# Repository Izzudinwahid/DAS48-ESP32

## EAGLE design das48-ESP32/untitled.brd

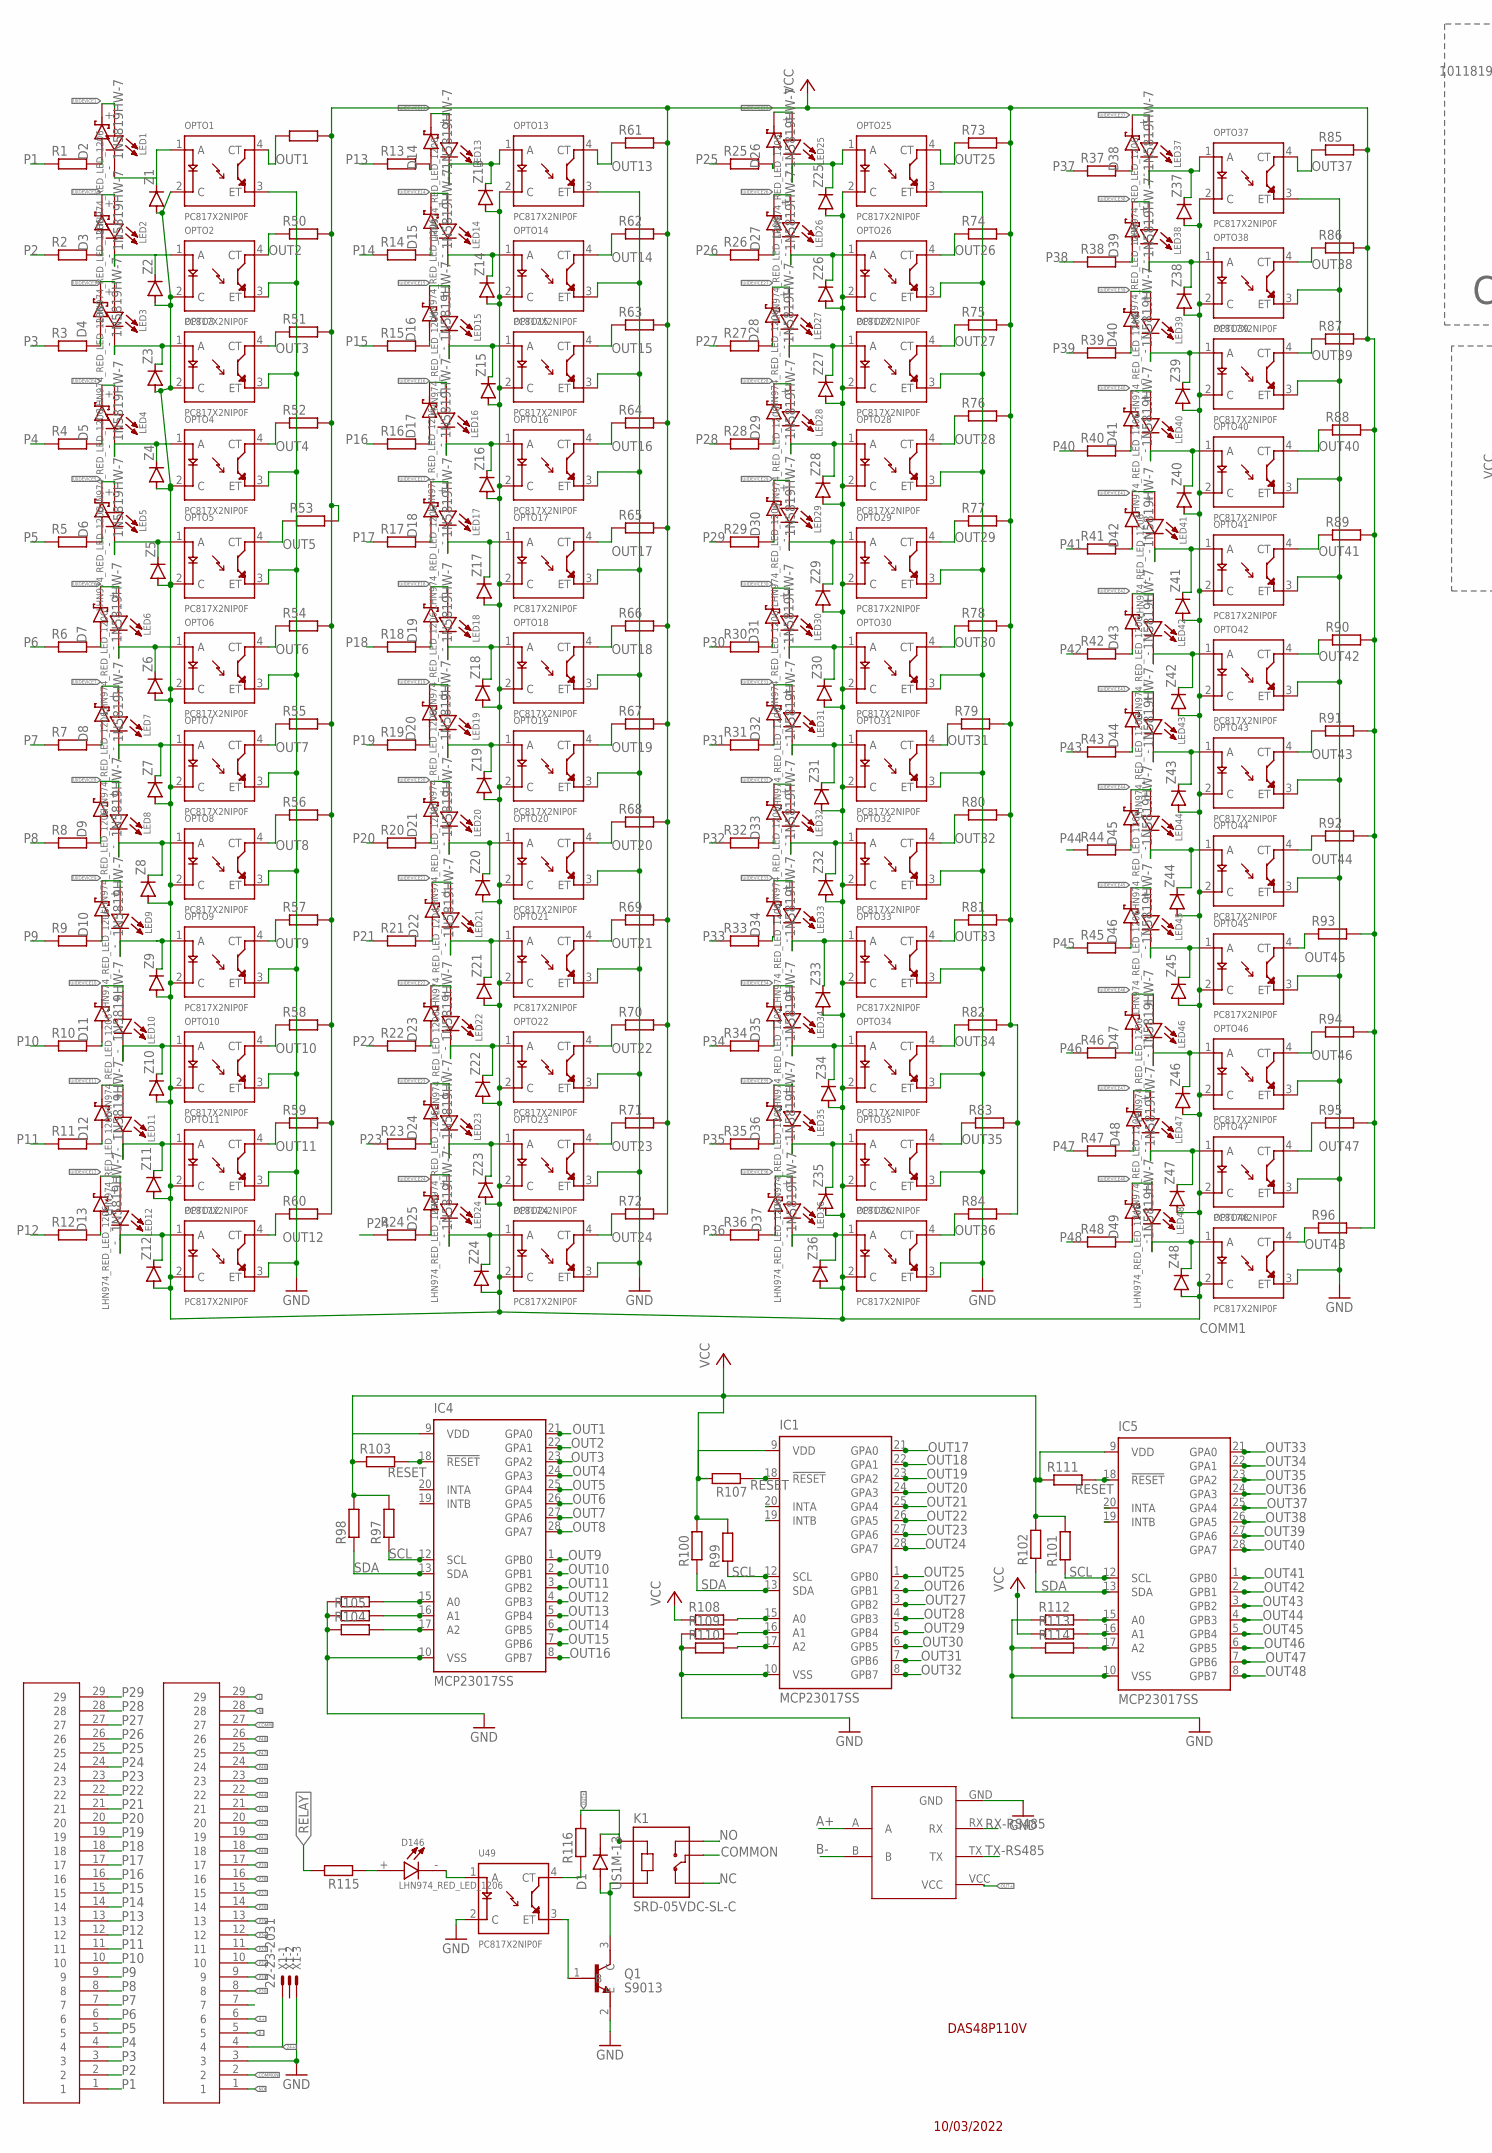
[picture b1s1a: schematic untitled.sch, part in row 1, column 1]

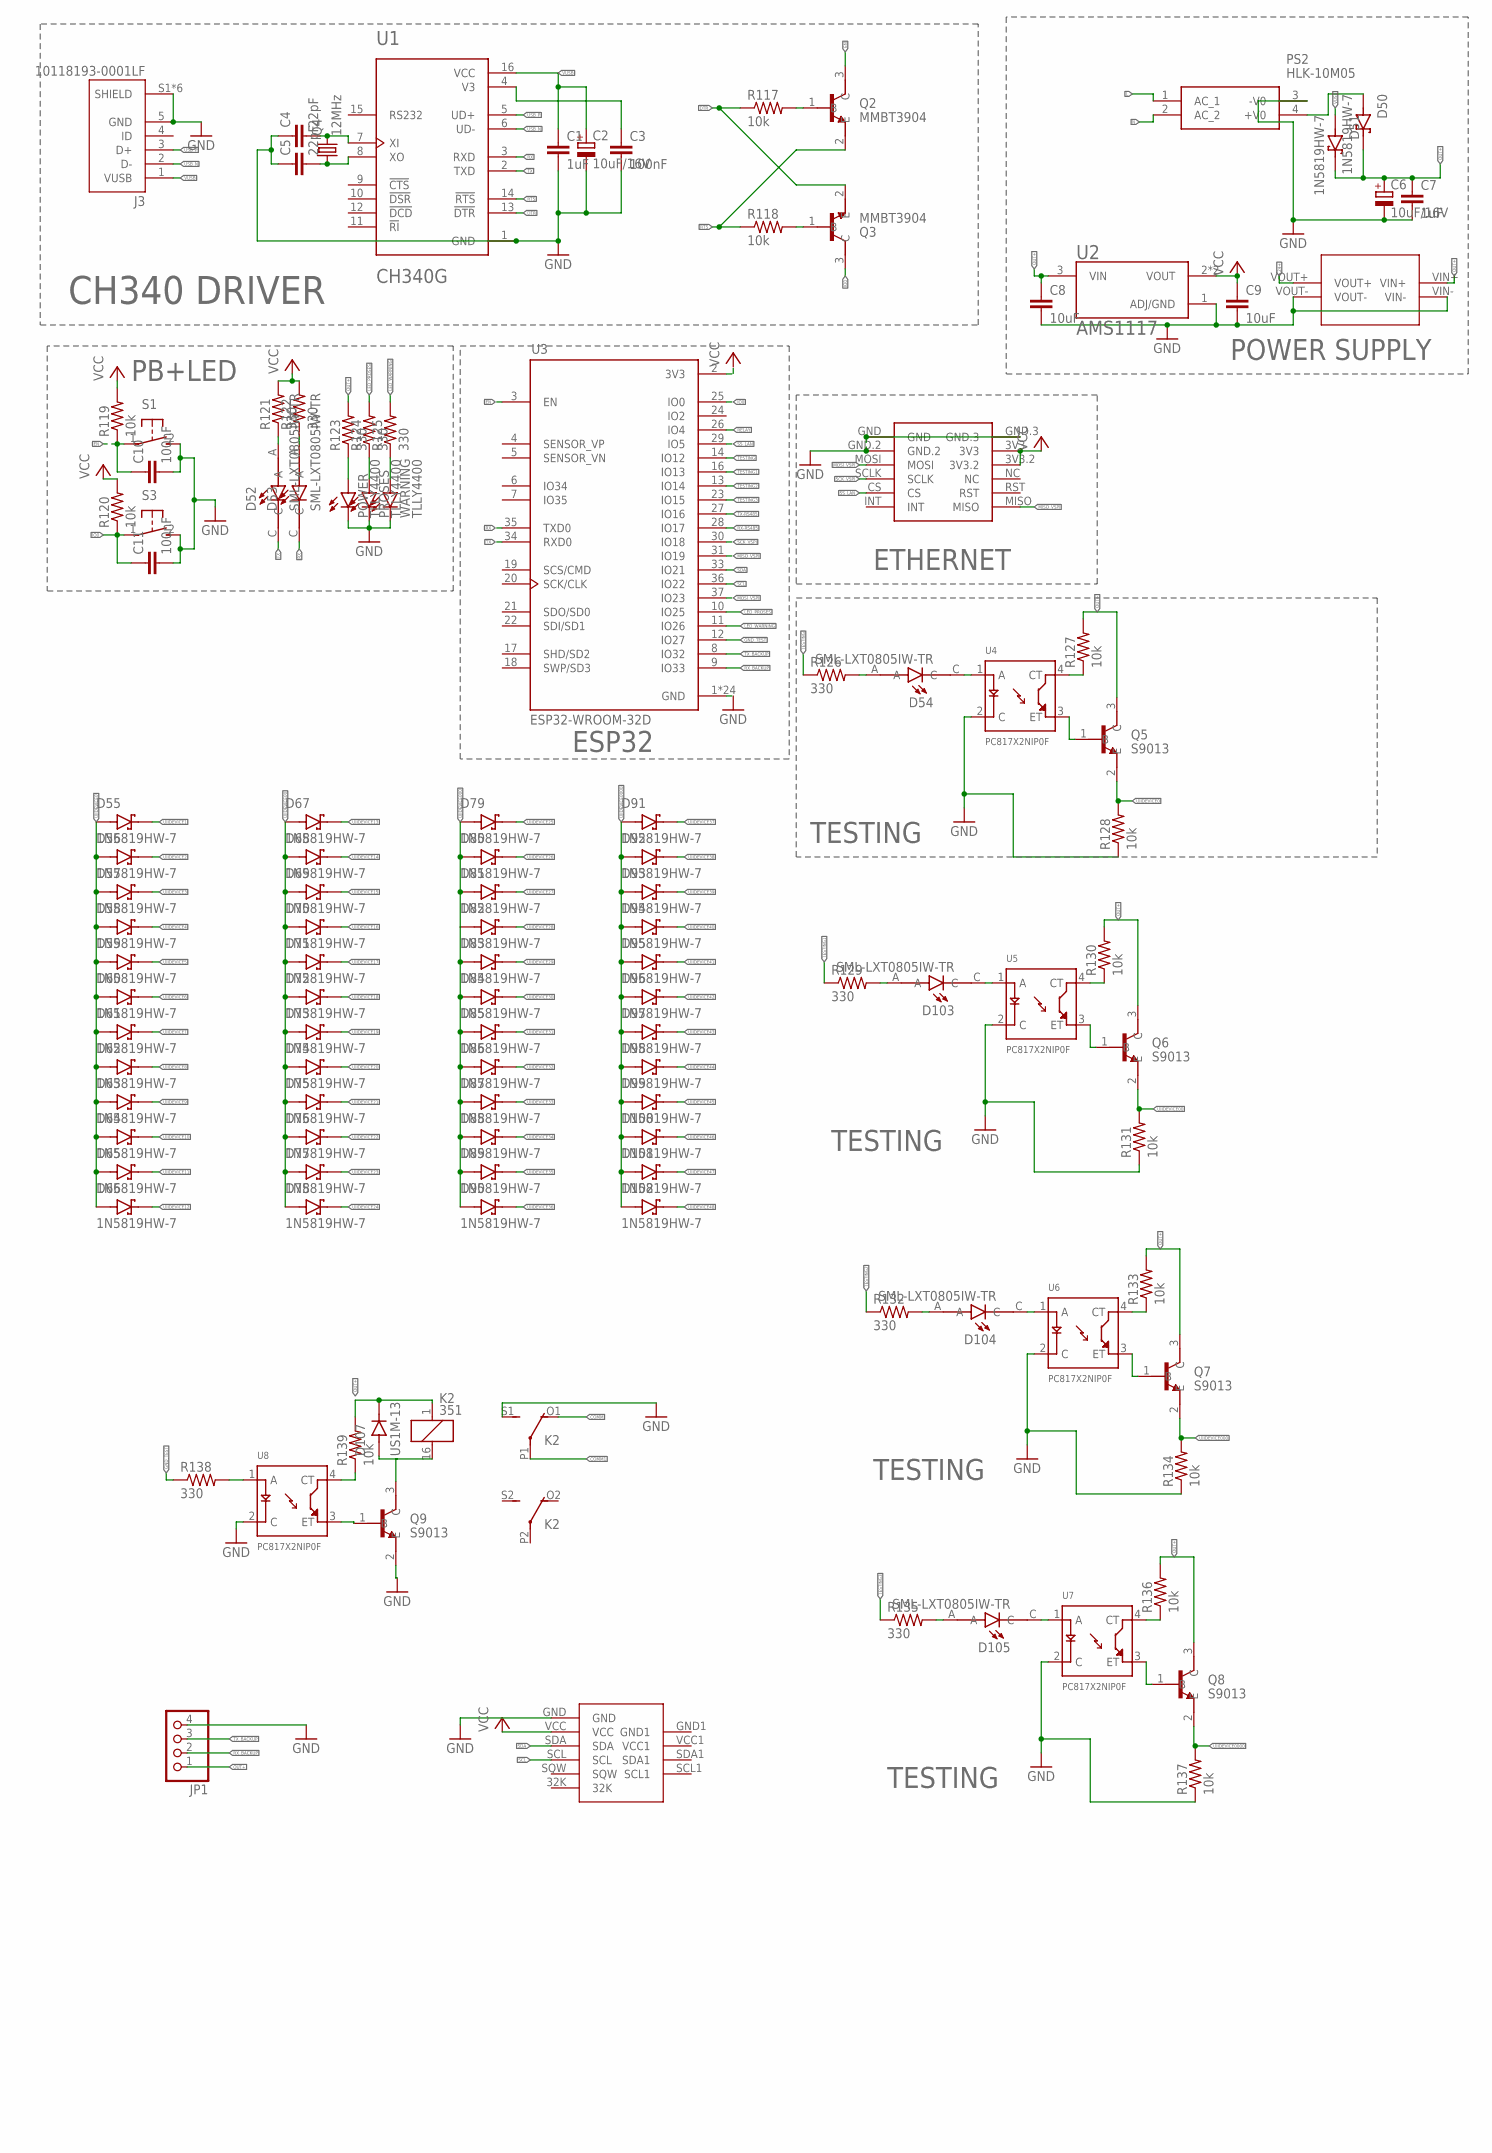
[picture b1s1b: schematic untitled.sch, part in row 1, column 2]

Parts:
C1, C7: 1uF; C0805K
C2, C6: 10uF/16V; 153CLV-0505
C3, C10, C11: 100nF; C0805K
C4, C5: 22pF; C0805K
C8, C9: 10uF; C0805K
D1, D107: US1M-13; DIOM5226X240N
D2, D3, D4, D5, D6, D7, D8, D9, D10, D11, D12, D13, D14, D15, D16, D17, D18, D19, D20, D21, D22, D23, D24, D25, D26, D27, D28, D29, D30, D31, D32, D33, D34, D35, D36, D37, D38, D39, D40, D41, D42, D43, D44, D45, D46, D47, D48, D49, D50, D51, D55, D56, D57, D58, D59, D60, D61, D62, D63, D64, D65, D66, D67, D68, D69, D70, D71, D72, D73, D74, D75, D76, D77, D78, D79, D80, D81, D82, D83, D84, D85, D86, D87, D88, D89, D90, D91, D92, D93, D94, D95, D96, D97, D98, D99, D100, D101, D102: 1N5819HW-7; SOD3715X145N
D52, D53, D54, D103, D104, D105: SML-LXT0805IW-TR; LEDC2012X120N
D146: LHN974_RED_LED_1206; LEDC3216X120N
HEADER-29P1, HEADER-29P2: HEADER-29P
IC1, IC4, IC5: MCP23017SS; SSOP28DB
J3: 10118193-0001LF; FCI_10118193-0001LF
JP1: PINHD-1X4; 1X04
K1: SRD-05VDC-SL-C; RELAY_SRD-05VDC-SL-C
K2: 351
LED1, LED2, LED3, LED4, LED5, LED6, LED7, LED8, LED9, LED10, LED11, LED12, LED13, LED14, LED15, LED16, LED17, LED18, LED19, LED20, LED21, LED22, LED23, LED24, LED25, LED26, LED27, LED28, LED29, LED30, LED31, LED32, LED33, LED34, LED35, LED36, LED37, LED38, LED39, LED40, LED41, LED42, LED43, LED44, LED45, LED46, LED47, LED48: LHN974_RED_LED_1206; LEDC3216X120N
MT1: MT3608
OPTO1, OPTO2, OPTO3, OPTO4, OPTO5, OPTO6, OPTO7, OPTO8, OPTO9, OPTO10, OPTO11, OPTO12, OPTO13, OPTO14, OPTO15, OPTO16, OPTO17, OPTO18, OPTO19, OPTO20, OPTO21, OPTO22, OPTO23, OPTO24, OPTO25, OPTO26, OPTO27, OPTO28, OPTO29, OPTO30, OPTO31, OPTO32, OPTO33, OPTO34, OPTO35, OPTO36, OPTO37, OPTO38, OPTO39, OPTO40, OPTO41, OPTO42, OPTO43, OPTO44, OPTO45, OPTO46, OPTO47, OPTO48: PC817X2NIP0F; SOT254P975X400-4N
POWER: TLLY4400; LED3MM
PROSES: TLLY4400; LED3MM
PS2: HLK-10M05; HLK10M05
Q1, Q5, Q6, Q7, Q8, Q9: S9013; SOT95P240X120-3N
Q2, Q3: MMBT3904; SOT95P240X120-3N
Q4: 12MHz; SM49
R1, R2, R3, R4, R5, R6, R7, R8, R9, R10, R11, R12, R13, R14, R15, R16, R17, R18, R19, R20, R21, R22, R23, R24, R25, R26, R27, R28, R29, R30, R31, R32, R33, R34, R35, R36, R37, R38, R39, R40, R41, R42, R43, R44, R45, R46, R47, R48: R-EU_0617/17; 0617/17
R49, R50, R51, R52, R53, R54, R55, R56, R57, R58, R59, R60, R61, R62, R63, R64, R65, R66, R67, R68, R69, R70, R71, R72, R73, R74, R75, R76, R77, R78, R79, R80, R81, R82, R83, R84, R85, R86, R87, R88, R89, R90, R91, R92, R93, R94, R95, R96, R97, R98, R99, R100, R101, R102, R103, R104, R105, R106, R107, R108, R109, R110, R111, R112, R113, R114, R115, R116: R-EU_R0805; R0805
R117, R118, R119, R120, R127, R128, R130, R131, R133, R134, R136, R137, R139: 10k; M0805
R121, R122, R123, R124, R125, R126, R129, R132, R135, R138: 330; M0805
RTC1: RTC3231
S1, S3: 31-XX; B3F-31XX
TTL-RS1: TTL-RS485
U1: CH340G; SOIC127P600X180-16N
U2: AMS1117; SOT229P700X180-4N
U3: ESP32-WROOM-32D; MODULE_ESP32-WROOM-32D
U4, U5, U6, U7, U8, U49: PC817X2NIP0F; SOT254P975X400-4N
U$1: MINI_W5500
WARNING: TLLY4400; LED3MM
X1: 22-23-2031
Z1, Z2, Z3, Z4, Z5, Z6, Z7, Z8, Z9, Z10, Z11, Z12, Z13, Z14, Z15, Z16, Z17, Z18, Z19, Z20, Z21, Z22, Z23, Z24, Z25, Z26, Z27, Z28, Z29, Z30, Z31, Z32, Z33, Z34, Z35, Z36, Z37, Z38, Z39, Z40, Z41, Z42, Z43, Z44, Z45, Z46, Z47, Z48: DIODE-SOD123; SOD123

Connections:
24+: HEADER-29P2.4, MT1.VOUT+, X1.1
A+: HEADER-29P2.6, TTL-RS1.A
B-: HEADER-29P2.5, TTL-RS1.B
COMM: HEADER-29P2.27, K2.O1 (O)
COMM1: K2.P1, OPTO1.2 (C), OPTO2.2 (C), OPTO3.2 (C), OPTO4.2 (C), OPTO5.2 (C), OPTO6.2 (C), OPTO7.2 (C), OPTO8.2 (C), OPTO9.2 (C), OPTO10.2 (C), OPTO11.2 (C), OPTO12.2 (C), OPTO13.2 (C), OPTO14.2 (C), OPTO15.2 (C), OPTO16.2 (C), OPTO17.2 (C), OPTO18.2 (C), OPTO19.2 (C), OPTO20.2 (C), OPTO21.2 (C), OPTO22.2 (C), OPTO23.2 (C), OPTO24.2 (C), OPTO25.2 (C), OPTO26.2 (C), OPTO27.2 (C), OPTO28.2 (C), OPTO29.2 (C), OPTO30.2 (C), OPTO31.2 (C), OPTO32.2 (C), OPTO33.2 (C), OPTO34.2 (C), OPTO35.2 (C), OPTO36.2 (C), OPTO37.2 (C), OPTO38.2 (C), OPTO39.2 (C), OPTO40.2 (C), OPTO41.2 (C), OPTO42.2 (C), OPTO43.2 (C), OPTO44.2 (C), OPTO45.2 (C), OPTO46.2 (C), OPTO47.2 (C), OPTO48.2 (C), Z1.A, Z2.A, Z3.A, Z4.A, Z5.A, Z6.A, Z7.A, Z8.A, Z9.A, Z10.A, Z11.A, Z12.A, Z13.A, Z14.A, Z15.A, Z16.A, Z17.A, Z18.A, Z19.A, Z20.A, Z21.A, Z22.A, Z23.A, Z24.A, Z25.A, Z26.A, Z27.A, Z28.A, Z29.A, Z30.A, Z31.A, Z32.A, Z33.A, Z34.A, Z35.A, Z36.A, Z37.A, Z38.A, Z39.A, Z40.A, Z41.A, Z42.A, Z43.A, Z44.A, Z45.A, Z46.A, Z47.A, Z48.A
COMMON: HEADER-29P2.2, K1.COM
DTR: Q3.2 (E), R117.1, U1.13 (!DTR)
EN: C10.1, Q2.3 (C), R119.1, S1.1, U3.3 (EN)
GND: C1.2, C2.-, C3.2, C4.1, C5.1, C6.-, C7.2, C8.2, C9.2, C10.2, C11.2, HEADER-29P2.3, IC1.10 (VSS), IC4.10 (VSS), IC5.10 (VSS), J3.5 (GND), J3.S1 (SHIELD), J3.S2 (SHIELD), J3.S3 (SHIELD), J3.S4 (SHIELD), J3.S5 (SHIELD), J3.S6 (SHIELD), JP1.4, K2.S1 (S), MT1.VIN-, MT1.VOUT-, OPTO1.3 (ET), OPTO2.3 (ET), OPTO3.3 (ET), OPTO4.3 (ET), OPTO5.3 (ET), OPTO6.3 (ET), OPTO7.3 (ET), OPTO8.3 (ET), OPTO9.3 (ET), OPTO10.3 (ET), OPTO11.3 (ET), OPTO12.3 (ET), OPTO13.3 (ET), OPTO14.3 (ET), OPTO15.3 (ET), OPTO16.3 (ET), OPTO17.3 (ET), OPTO18.3 (ET), OPTO19.3 (ET), OPTO20.3 (ET), OPTO21.3 (ET), OPTO22.3 (ET), OPTO23.3 (ET), OPTO24.3 (ET), OPTO25.3 (ET), OPTO26.3 (ET), OPTO27.3 (ET), OPTO28.3 (ET), OPTO29.3 (ET), OPTO30.3 (ET), OPTO31.3 (ET), OPTO32.3 (ET), OPTO33.3 (ET), OPTO34.3 (ET), OPTO35.3 (ET), OPTO36.3 (ET), OPTO37.3 (ET), OPTO38.3 (ET), OPTO39.3 (ET), OPTO40.3 (ET), OPTO41.3 (ET), OPTO42.3 (ET), OPTO43.3 (ET), OPTO44.3 (ET), OPTO45.3 (ET), OPTO46.3 (ET), OPTO47.3 (ET), OPTO48.3 (ET), POWER.K (C), PROSES.K (C), PS2.3 (-V0), Q1.2 (E), Q9.2 (E), R104.1, R105.1, R106.1, R109.1, R110.1, R112.1, R114.1, R128.1, R131.1, R134.1, R137.1, RTC1.GND, S1.2 (S), S3.2 (S), TTL-RS1.GND, U1.1 (GND), U2.1 (ADJ/GND), U3.1 (GND), U3.15 (GND), U3.38 (GND), U3.39_1 (GND), U3.39_2 (GND), U3.39_3 (GND), U3.39_4 (GND), U3.39_5 (GND), U3.39_6 (GND), U3.39_7 (GND), U3.39_8 (GND), U3.39_9 (GND), U3.39_10 (GND), U3.39_11 (GND), U3.39_12 (GND), U3.39_13 (GND), U3.39_14 (GND), U3.39_15 (GND), U3.39_16 (GND), U3.39_17 (GND), U3.39_18 (GND), U3.39_19 (GND), U3.39_20 (GND), U3.39_21 (GND), U4.2 (C), U5.2 (C), U6.2 (C), U7.2 (C), U8.2 (C), U49.2 (C), U$1.GND, U$1.GND.2, U$1.GND.3, WARNING.K (C), X1.3
GND_TEST: R138.1, U3.12 (IO27)
IO0: C11.1, Q3.3 (C), R120.1, S3.1, U3.25 (IO0)
L: HEADER-29P2.29, PS2.1 (AC_1)
LED_PROSES: R124.2, U3.10 (IO25)
LED_WARNING: R125.2, U3.11 (IO26)
MISO_VSPI: U3.31 (IO19), U$1.MISO
MOSI_VSPI: U3.37 (IO23), U$1.MOSI
N: HEADER-29P2.28, PS2.2 (AC_2)
unnamed: D2.A, R1.2
unnamed: D50.A, PS2.4 (+V0)
unnamed: D3.A, R2.2
unnamed: Q5.1 (B), U4.3 (ET)
unnamed: D4.A, R3.2
unnamed: R127.1, U4.4 (CT)
unnamed: D5.A, R4.2
unnamed: D103.A, R129.2
unnamed: D6.A, R5.2
unnamed: D103.C, U5.1 (A)
unnamed: D7.A, R6.2
unnamed: Q6.1 (B), U5.3 (ET)
unnamed: D8.A, R7.2
unnamed: R130.1, U5.4 (CT)
unnamed: D9.A, R8.2
unnamed: D104.A, R132.2
unnamed: D15.A, R14.2
unnamed: LED1.-, OPTO1.1 (A), Z1.C
unnamed: LED13.-, OPTO13.1 (A), Z13.C
unnamed: D10.A, R9.2
unnamed: LED14.-, OPTO14.1 (A), Z14.C
unnamed: D104.C, U6.1 (A)
unnamed: LED15.-, OPTO15.1 (A), Z15.C
unnamed: D11.A, R10.2
unnamed: LED16.-, OPTO16.1 (A), Z16.C
unnamed: Q7.1 (B), U6.3 (ET)
unnamed: LED17.-, OPTO17.1 (A), Z17.C
unnamed: D12.A, R11.2
unnamed: LED18.-, OPTO18.1 (A), Z18.C
unnamed: R133.1, U6.4 (CT)
unnamed: LED19.-, OPTO19.1 (A), Z19.C
unnamed: LED20.-, OPTO20.1 (A), Z20.C
unnamed: LED21.-, OPTO21.1 (A), Z21.C
unnamed: D105.A, R135.2
unnamed: LED22.-, OPTO22.1 (A), Z22.C
unnamed: D13.A, R12.2
unnamed: LED23.-, OPTO23.1 (A), Z23.C
unnamed: D105.C, U7.1 (A)
unnamed: LED24.-, OPTO24.1 (A), Z24.C
unnamed: D14.A, R13.2
unnamed: LED25.-, OPTO25.1 (A), Z25.C
unnamed: Q8.1 (B), U7.3 (ET)
unnamed: LED26.-, OPTO26.1 (A), Z26.C
unnamed: D16.A, R15.2
unnamed: LED27.-, OPTO27.1 (A), Z27.C
unnamed: R136.1, U7.4 (CT)
unnamed: LED28.-, OPTO28.1 (A), Z28.C
unnamed: D17.A, R16.2
unnamed: LED29.-, OPTO29.1 (A), Z29.C
unnamed: LED30.-, OPTO30.1 (A), Z30.C
unnamed: D18.A, R17.2
unnamed: LED31.-, OPTO31.1 (A), Z31.C
unnamed: R138.2, U8.1 (A)
unnamed: LED32.-, OPTO32.1 (A), Z32.C
unnamed: D19.A, R18.2
unnamed: LED33.-, OPTO33.1 (A), Z33.C
unnamed: R139.1, U8.4 (CT)
unnamed: LED34.-, OPTO34.1 (A), Z34.C
unnamed: D20.A, R19.2
unnamed: LED35.-, OPTO35.1 (A), Z35.C
unnamed: Q9.1 (B), U8.3 (ET)
unnamed: LED36.-, OPTO36.1 (A), Z36.C
unnamed: D32.A, R31.2
unnamed: LED37.-, OPTO37.1 (A), Z37.C
unnamed: D21.A, R20.2
unnamed: LED38.-, OPTO38.1 (A), Z38.C
unnamed: LED39.-, OPTO39.1 (A), Z39.C
unnamed: LED40.-, OPTO40.1 (A), Z40.C
unnamed: D22.A, R21.2
unnamed: LED41.-, OPTO41.1 (A), Z41.C
unnamed: D107.A, K2.16 (2), Q9.3 (C)
unnamed: LED42.-, OPTO42.1 (A), Z42.C
unnamed: LED43.-, OPTO43.1 (A), Z43.C
unnamed: D23.A, R22.2
unnamed: LED44.-, OPTO44.1 (A), Z44.C
unnamed: LED45.-, OPTO45.1 (A), Z45.C
unnamed: D24.A, R23.2
unnamed: LED46.-, OPTO46.1 (A), Z46.C
unnamed: LED47.-, OPTO47.1 (A), Z47.C
unnamed: D25.A, R24.2
unnamed: LED48.-, OPTO48.1 (A), Z48.C
unnamed: LED2.-, OPTO2.1 (A), Z2.C
unnamed: LED3.-, OPTO3.1 (A), Z3.C
unnamed: LED4.-, OPTO4.1 (A), Z4.C
unnamed: LED5.-, OPTO5.1 (A), Z5.C
unnamed: LED6.-, OPTO6.1 (A), Z6.C
unnamed: LED7.-, OPTO7.1 (A), Z7.C
unnamed: LED8.-, OPTO8.1 (A), Z8.C
unnamed: LED9.-, OPTO9.1 (A), Z9.C
unnamed: LED10.-, OPTO10.1 (A), Z10.C
unnamed: LED11.-, OPTO11.1 (A), Z11.C
unnamed: LED12.-, OPTO12.1 (A), Z12.C
unnamed: D146.-, U49.1 (A)
unnamed: D146.+, R115.1
unnamed: R116.1, U49.4 (CT)
unnamed: IC5.15 (A0), R112.2
unnamed: D1.A, K1.A2, Q1.3 (C)
unnamed: Q1.1 (B), U49.3 (ET)
unnamed: IC5.16 (A1), R113.2
unnamed: D26.A, R25.2
unnamed: IC1.15 (A0), R108.2
unnamed: IC1.16 (A1), R109.2
unnamed: IC4.15 (A0), R106.2
unnamed: IC4.16 (A1), R105.2
unnamed: IC4.17 (A2), R104.2
unnamed: IC5.17 (A2), R114.2
unnamed: IC1.17 (A2), R110.2
unnamed: D27.A, R26.2
unnamed: D28.A, R27.2
unnamed: D29.A, R28.2
unnamed: D30.A, R29.2
unnamed: D31.A, R30.2
unnamed: D33.A, R32.2
unnamed: D35.A, R34.2
unnamed: D36.A, R35.2
unnamed: D42.A, R41.2
unnamed: D37.A, R36.2
unnamed: D38.A, R37.2
unnamed: D34.A, R33.2
unnamed: D39.A, R38.2
unnamed: D40.A, R39.2
unnamed: D41.A, R40.2
unnamed: D43.A, R42.2
unnamed: D44.A, R43.2
unnamed: D45.A, R44.2
unnamed: D46.A, R45.2
unnamed: D47.A, R46.2
unnamed: D54.A, R126.2
unnamed: D54.C, U4.1 (A)
unnamed: D48.A, R47.2
unnamed: D49.A, R48.2
unnamed: C3.1, U1.4 (V3)
unnamed: C4.2, Q4.2, U1.7 (XI)
unnamed: C5.2, Q4.1, U1.8 (XO)
unnamed: POWER.A, R123.1
unnamed: PROSES.A, R124.1
unnamed: Q2.1 (B), R117.2
unnamed: Q3.1 (B), R118.2
unnamed: R125.1, WARNING.A
unnamed: D52.A, R121.1
unnamed: D53.A, R122.1
NC: K1.NC
NO: HEADER-29P2.1, K1.NO
OUT1: IC4.21 (GPA0), OPTO1.4 (CT), R49.1
OUT2: IC4.22 (GPA1), OPTO2.4 (CT), R50.1
OUT3: IC4.23 (GPA2), OPTO3.4 (CT), R51.1
OUT4: IC4.24 (GPA3), OPTO4.4 (CT), R52.1
OUT5: IC4.25 (GPA4), OPTO5.4 (CT), R53.1
OUT6: IC4.26 (GPA5), OPTO6.4 (CT), R54.1
OUT7: IC4.27 (GPA6), OPTO7.4 (CT), R55.1
OUT8: IC4.28 (GPA7), OPTO8.4 (CT), R56.1
OUT9: IC4.1 (GPB0), OPTO9.4 (CT), R57.1
OUT10: IC4.2 (GPB1), OPTO10.4 (CT), R58.1
OUT11: IC4.3 (GPB2), OPTO11.4 (CT), R59.1
OUT12: IC4.4 (GPB3), OPTO12.4 (CT), R60.1
OUT13: IC4.5 (GPB4), OPTO13.4 (CT), R61.1
OUT14: IC4.6 (GPB5), OPTO14.4 (CT), R62.1
OUT15: IC4.7 (GPB6), OPTO15.4 (CT), R63.1
OUT16: IC4.8 (GPB7), OPTO16.4 (CT), R64.1
OUT17: IC1.21 (GPA0), OPTO17.4 (CT), R65.1
OUT18: IC1.22 (GPA1), OPTO18.4 (CT), R66.1
OUT19: IC1.23 (GPA2), OPTO19.4 (CT), R67.1
OUT20: IC1.24 (GPA3), OPTO20.4 (CT), R68.1
OUT21: IC1.25 (GPA4), OPTO21.4 (CT), R69.1
OUT22: IC1.26 (GPA5), OPTO22.4 (CT), R70.1
OUT23: IC1.27 (GPA6), OPTO23.4 (CT), R71.1
OUT24: IC1.28 (GPA7), OPTO24.4 (CT), R72.1
OUT25: IC1.1 (GPB0), OPTO25.4 (CT), R73.1
OUT26: IC1.2 (GPB1), OPTO26.4 (CT), R74.1
OUT27: IC1.3 (GPB2), OPTO27.4 (CT), R75.1
OUT28: IC1.4 (GPB3), OPTO28.4 (CT), R76.1
OUT29: IC1.5 (GPB4), OPTO29.4 (CT), R77.1
OUT30: IC1.6 (GPB5), OPTO30.4 (CT), R78.1
OUT31: IC1.7 (GPB6), OPTO31.4 (CT), R79.1
OUT32: IC1.8 (GPB7), OPTO32.4 (CT), R80.1
OUT33: IC5.21 (GPA0), OPTO33.4 (CT), R81.1
OUT34: IC5.22 (GPA1), OPTO34.4 (CT), R82.1
OUT35: IC5.23 (GPA2), OPTO35.4 (CT), R83.1
OUT36: IC5.24 (GPA3), OPTO36.4 (CT), R84.1
OUT37: IC5.25 (GPA4), OPTO37.4 (CT), R85.1
OUT38: IC5.26 (GPA5), OPTO38.4 (CT), R86.1
OUT39: IC5.27 (GPA6), OPTO39.4 (CT), R87.1
OUT40: IC5.28 (GPA7), OPTO40.4 (CT), R88.1
OUT41: IC5.1 (GPB0), OPTO41.4 (CT), R89.1
OUT42: IC5.2 (GPB1), OPTO42.4 (CT), R90.1
OUT43: IC5.3 (GPB2), OPTO43.4 (CT), R91.1
OUT44: IC5.4 (GPB3), OPTO44.4 (CT), R92.1
OUT45: IC5.5 (GPB4), OPTO45.4 (CT), R93.1
OUT46: IC5.6 (GPB5), OPTO46.4 (CT), R94.1
OUT47: IC5.7 (GPB6), OPTO47.4 (CT), R95.1
OUT48: IC5.8 (GPB7), OPTO48.4 (CT), R96.1
OUT+: C6.+, C7.1, C8.1, D1.C (K), D50.C (K), D51.C (K), D107.C (K), JP1.1, K1.A1, K2.1, MT1.VIN+, Q5.3 (C), Q6.3 (C), Q7.3 (C), Q8.3 (C), R116.2, R123.2, R127.2, R130.2, R133.2, R136.2, R139.2, TTL-RS1.VCC, U2.3 (VIN)
P1: HEADER-29P1.1, R1.1
P2: HEADER-29P1.2, R2.1
P3: HEADER-29P1.3, R3.1
P4: HEADER-29P1.4, R4.1
P5: HEADER-29P1.5, R5.1
P6: HEADER-29P1.6, R6.1
P7: HEADER-29P1.7, R7.1
P8: HEADER-29P1.8, R8.1
P9: HEADER-29P1.9, R9.1
P10: HEADER-29P1.10, R10.1
P11: HEADER-29P1.11, R11.1
P12: HEADER-29P1.12, R12.1
P13: HEADER-29P1.13, R13.1
P14: HEADER-29P1.14, R14.1
P15: HEADER-29P1.15, R15.1
P16: HEADER-29P1.16, R16.1
P17: HEADER-29P1.17, R17.1
P18: HEADER-29P1.18, R18.1
P19: HEADER-29P1.19, R19.1
P20: HEADER-29P1.20, R20.1
P21: HEADER-29P1.21, R21.1
P22: HEADER-29P1.22, R22.1
P23: HEADER-29P1.23, R23.1
P24: HEADER-29P1.24, R24.1
P25: HEADER-29P1.25, R25.1
P26: HEADER-29P1.26, R26.1
P27: HEADER-29P1.27, R27.1
P28: HEADER-29P1.28, R28.1
P29: HEADER-29P1.29, R29.1
P30: HEADER-29P2.8, R30.1
P31: HEADER-29P2.9, R31.1
P32: HEADER-29P2.10, R32.1
P33: HEADER-29P2.11, R33.1
P34: HEADER-29P2.12, R34.1
P35: HEADER-29P2.13, R35.1
P36: HEADER-29P2.14, R36.1
P37: HEADER-29P2.15, R37.1
P38: HEADER-29P2.16, R38.1
P39: HEADER-29P2.17, R39.1
P40: HEADER-29P2.18, R40.1
P41: HEADER-29P2.19, R41.1
P42: HEADER-29P2.20, R42.1
P43: HEADER-29P2.21, R43.1
P44: HEADER-29P2.22, R44.1
P45: HEADER-29P2.23, R45.1
P46: HEADER-29P2.24, R46.1
P47: HEADER-29P2.25, R47.1
P48: HEADER-29P2.26, R48.1
RELAY: R115.2, U3.26 (IO4)
RESET: IC1.18 (!RESET), IC4.18 (!RESET), IC5.18 (!RESET), R103.2, R107.1, R111.2
RTS: Q2.2 (E), R118.1, U1.14 (!RTS)
RX: D53.C, U1.3 (RXD), U3.35 (TXD0)
RX-RS485: TTL-RS1.RX, U3.28 (IO17)
RX_BACKUP: JP1.2, U3.9 (IO33)
SCK_VSPI: U3.30 (IO18), U$1.SCLK
SCL: IC1.12 (SCL), IC4.12 (SCL), IC5.12 (SCL), R97.1, R99.1, R101.1, RTC1.SCL, U3.36 (IO22)
SDA: IC1.13 (SDA), IC4.13 (SDA), IC5.13 (SDA), R98.1, R100.1, R102.1, RTC1.SDA, U3.33 (IO21)
SS_LAN: U3.29 (IO5), U$1.CS
TESTING: R126.1, U3.14 (IO12)
TESTING1: R129.1, U3.16 (IO13)
TESTING2: R132.1, U3.13 (IO14)
TESTING3: R135.1, U3.23 (IO15)
TX: D52.C, U1.2 (TXD), U3.34 (RXD0)
TX-RS485: TTL-RS1.TX, U3.27 (IO16)
TX_BACKUP: JP1.3, U3.8 (IO32)
UJIDEVICE0: D55.A, D56.A, D57.A, D58.A, D59.A, D60.A, D61.A, D62.A, D63.A, D64.A, D65.A, D66.A, Q5.2 (E), R128.2
UJIDEVICE00: D67.A, D68.A, D69.A, D70.A, D71.A, D72.A, D73.A, D74.A, D75.A, D76.A, D77.A, D78.A, Q6.2 (E), R131.2
UJIDEVICE000: D79.A, D80.A, D81.A, D82.A, D83.A, D84.A, D85.A, D86.A, D87.A, D88.A, D89.A, D90.A, Q7.2 (E), R134.2
UJIDEVICE0000: D91.A, D92.A, D93.A, D94.A, D95.A, D96.A, D97.A, D98.A, D99.A, D100.A, D101.A, D102.A, Q8.2 (E), R137.2
UJIDEVICE1: D2.C (K), D55.C (K), LED1.+
UJIDEVICE2: D3.C (K), D56.C (K), LED2.+
UJIDEVICE3: D4.C (K), D57.C (K), LED3.+
UJIDEVICE4: D5.C (K), D58.C (K), LED4.+
UJIDEVICE5: D6.C (K), D59.C (K), LED5.+
UJIDEVICE6: D7.C (K), D60.C (K), LED6.+
UJIDEVICE7: D8.C (K), D61.C (K), LED7.+
UJIDEVICE8: D9.C (K), D62.C (K), LED8.+
UJIDEVICE9: D10.C (K), D63.C (K), LED9.+
UJIDEVICE10: D11.C (K), D64.C (K), LED10.+
UJIDEVICE11: D12.C (K), D65.C (K), LED11.+
UJIDEVICE12: D13.C (K), D66.C (K), LED12.+
UJIDEVICE13: D14.C (K), D67.C (K), LED13.+
UJIDEVICE14: D15.C (K), D68.C (K), LED14.+
UJIDEVICE15: D16.C (K), D69.C (K), LED15.+
UJIDEVICE16: D17.C (K), D70.C (K), LED16.+
UJIDEVICE17: D18.C (K), D71.C (K), LED17.+
UJIDEVICE18: D19.C (K), D72.C (K), LED18.+
UJIDEVICE19: D20.C (K), D73.C (K), LED19.+
UJIDEVICE20: D21.C (K), D74.C (K), LED20.+
UJIDEVICE21: D22.C (K), D75.C (K), LED21.+
UJIDEVICE22: D23.C (K), D76.C (K), LED22.+
UJIDEVICE23: D24.C (K), D77.C (K), LED23.+
UJIDEVICE24: D25.C (K), D78.C (K), LED24.+
UJIDEVICE25: D26.C (K), D79.C (K), LED25.+
UJIDEVICE26: D27.C (K), D80.C (K), LED26.+
UJIDEVICE27: D28.C (K), D81.C (K), LED27.+
UJIDEVICE28: D29.C (K), D82.C (K), LED28.+
UJIDEVICE29: D30.C (K), D83.C (K), LED29.+
UJIDEVICE30: D31.C (K), D84.C (K), LED30.+
UJIDEVICE31: D32.C (K), D85.C (K), LED31.+
UJIDEVICE32: D33.C (K), D86.C (K), LED32.+
UJIDEVICE33: D34.C (K), D87.C (K), LED33.+
UJIDEVICE34: D35.C (K), D88.C (K), LED34.+
UJIDEVICE35: D36.C (K), D89.C (K), LED35.+
UJIDEVICE36: D37.C (K), D90.C (K), LED36.+
UJIDEVICE37: D38.C (K), D91.C (K), LED37.+
UJIDEVICE38: D39.C (K), D92.C (K), LED38.+
UJIDEVICE39: D40.C (K), D93.C (K), LED39.+
UJIDEVICE40: D41.C (K), D94.C (K), LED40.+
UJIDEVICE41: D42.C (K), D95.C (K), LED41.+
UJIDEVICE42: D43.C (K), D96.C (K), LED42.+
UJIDEVICE43: D44.C (K), D97.C (K), LED43.+
UJIDEVICE44: D45.C (K), D98.C (K), LED44.+
UJIDEVICE45: D46.C (K), D99.C (K), LED45.+
UJIDEVICE46: D47.C (K), D100.C (K), LED46.+
UJIDEVICE47: D48.C (K), D101.C (K), LED47.+
UJIDEVICE48: D49.C (K), D102.C (K), LED48.+
USB_N: J3.2 (D-), U1.6 (UD-)
USB_P: J3.3 (D+), U1.5 (UD+)
VCC: C9.1, IC1.9 (VDD), IC4.9 (VDD), IC5.9 (VDD), R49.2, R50.2, R51.2, R52.2, R53.2, R54.2, R55.2, R56.2, R57.2, R58.2, R59.2, R60.2, R61.2, R62.2, R63.2, R64.2, R65.2, R66.2, R67.2, R68.2, R69.2, R70.2, R71.2, R72.2, R73.2, R74.2, R75.2, R76.2, R77.2, R78.2, R79.2, R80.2, R81.2, R82.2, R83.2, R84.2, R85.2, R86.2, R87.2, R88.2, R89.2, R90.2, R91.2, R92.2, R93.2, R94.2, R95.2, R96.2, R97.2, R98.2, R99.2, R100.2, R101.2, R102.2, R103.1, R107.2, R108.1, R111.1, R113.1, R119.2, R120.2, R121.2, R122.2, RTC1.VCC, U2.2 (VOUT), U2.4 (VOUT), U3.2 (3V3), U$1.3V3, U$1.3V3.2
VUSB: C1.1, C2.+, D51.A, J3.1 (VUSB), U1.16 (VCC)

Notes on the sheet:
DAS48P110V
10/03/2022
CH340 DRIVER
POWER SUPPLY
PB+LED
ESP32
TESTING
ETHERNET

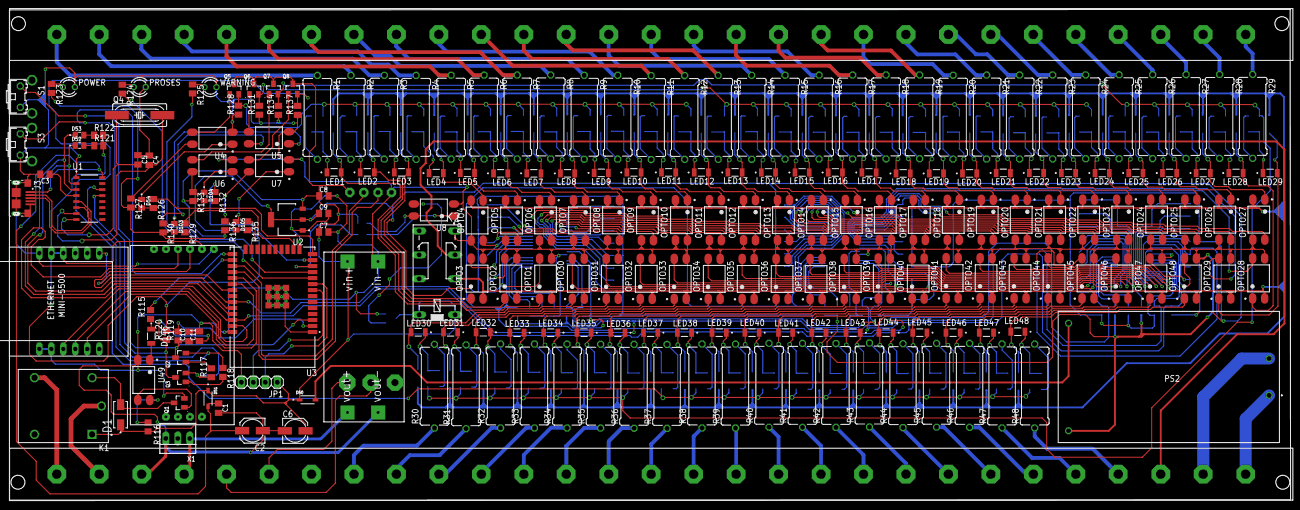
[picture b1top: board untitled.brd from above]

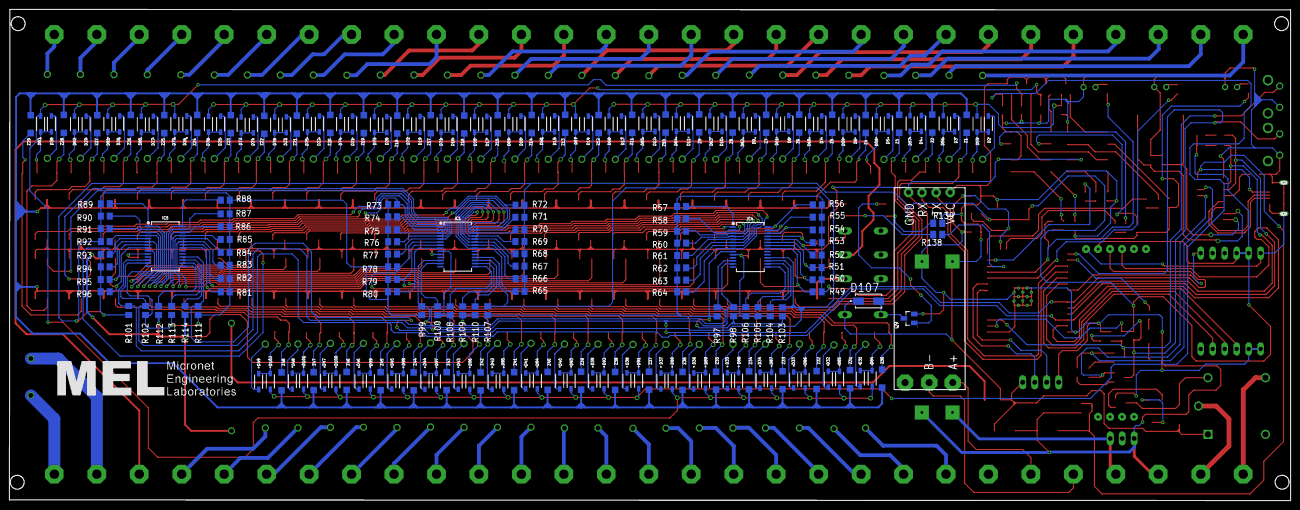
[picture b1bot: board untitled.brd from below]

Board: 2 copper layers, 271.6 x 104.1 mm, 439 parts (218 on the bottom side), 329 nets.

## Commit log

2023-01-12 rangkaian DAS48 dengan ESP32
2023-01-12 menambahkan label
2023-02-09 revisi tanggal 09/02/2023(revisi mas naufal)
